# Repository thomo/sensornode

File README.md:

# SensorNode

A ESP8266 based solution with support for

- DS18B20 1-Wire temperature sensor
- BME280 humidity, pressure, temperature sensor (I2C) - Note: temperature is measured in-chip, so it is usually too inaccurate to measure the environment temperature
- Si7021 humidity, temperatur sensor (I2C)
- HTU21 humidity, temperatur sensor (I2C)
- LDR sensors to "measure" the brightness (analog)

The software will determine which sensors are connected. Because of the fixed I2C addresses on the sensors only one example of BME, Si7021, or HTU21 can be connected - but multiple different. Multiple 1-Wire sensors are supported. In total the number of sensors is set to 10 (`main.cpp`__MAX_SENSORS__) - but please note that each measurand counts, e.g. a BME280 counts 3x.

The software provides an configuration web page where the sensors can be enabled and an location can be specified.

The ESP will than read the sensors every 10 seconds (can be changed in config dialog). The values are published via MQTT (`main.cpp` __MQTT_SERVER__). The used MQTT topic can be configured by the configuration web page (see below).

## Compile time configuration

There are some values which are only configureable on compile time (in `main.cpp`).

- DEFAULT_NODE_NAME (= F42-NODE) - used as WiFi SSID
- MQTT_SERVER (= mqtt.thomo.de) - the MQTT server, you will have to use your own :wink:
- DEFAULT_ROOT_TOPIC (= "tmp") - the standard root topic
- MAX_SENSORS (= 10) - number of supported sensors

## Runtime configuration

The runtime configuration is done by using a configuration web page served by the node. Just enter *`http://<node-ip>`*.

The config dialog allows you to enable/disable (aka activate) the connected sensors, only active sensor values are MQTT published.
For each sensor a location can be defined and a correction value. The correction value is add/sub from the sensor value and is used to calibrate the sensor.

*Note:* The displayed sensor value and the value published at MQTT already include the correction value.

## API

The Sensor Node offers some URIs

- `http://<node-ip>/config` - the node name, root topic, altitude, and display flag, as JSON data
- `http://<node-ip>/sensors` - the sensor data, as JSON

## MQTT Topic and Payload

The node will acquire the sensor measurements every X seconds - wether or not the sensor is enabled. It will than publish the value to the MQTT server with:

- topic: `<root topic>/<location>` - where each dot '.' in the root topic and in location is replaced by a slash.
  
  E.g.: with root topic *homebase* and sensor location *ground.kitchen* the resulting topic is `homebase/ground/kitchen`.
- payload: `<measurand>,location=<sensor location>,node=<node name>,sensor=<sensor type> value=<sensor value>`

  E.g.: for the selected DS18B20 sensor above the payload is `temperature,location=upstairs.workroom,node=f42,sensor=DS18B20 value=25.25`

## Circuit and PCB designs

### Sensors

- I2C Sensors
  - SDA -> GPIO4 (D2)
  - SCL -> GPIO5 (D1)
- 1wire
  - DATA -> GPIO0 (D3)
- LDR
  - ADC (Pin2)

### Display

- ST7735 -> ESP8266
  - 1 - RST -> RST or +3V3
  - 2 - CS  -> GPIO15 (D8)  
  - 3 - D/C -> GPIO2 (D4)
  - 4 - DIN -> GPI13 (D7)
  - 5 - CLK -> GPI14 (D5)
  - 6 - VCC -> +3V3
  - 7 - BL  -> +3V3
  - 8 - GND -> GND

__Note:__ _GPIO12 (D6) is not connected but is part of the SPI interface._

### SensorNodeUsb

It is a board to be used with the sensor node code. The board is designed to be simply plugged in an USB port.

If you want to order some pcb boards you can use this link to [Aisler](https://aisler.net/p/KDLFHCIK).

### SensorNodeCat

Another board I designed to be placed in a CAT box, but it can also be used in a more general way.

If you want to order some pcb boards you can use this link to [Aisler](
https://aisler.net/p/CNWEPDIW).

## Fonts/Icons

- Font: [Landasans](https://www.fontspace.com/search?q=landasans)
- Icons:
  - https://iconarchive.com/search?q=weather&page=6
  - https://www.elegantthemes.com/blog/freebie-of-the-week/beautiful-flat-icons-for-free
  - http://paomedia.github.io/small-n-flat/

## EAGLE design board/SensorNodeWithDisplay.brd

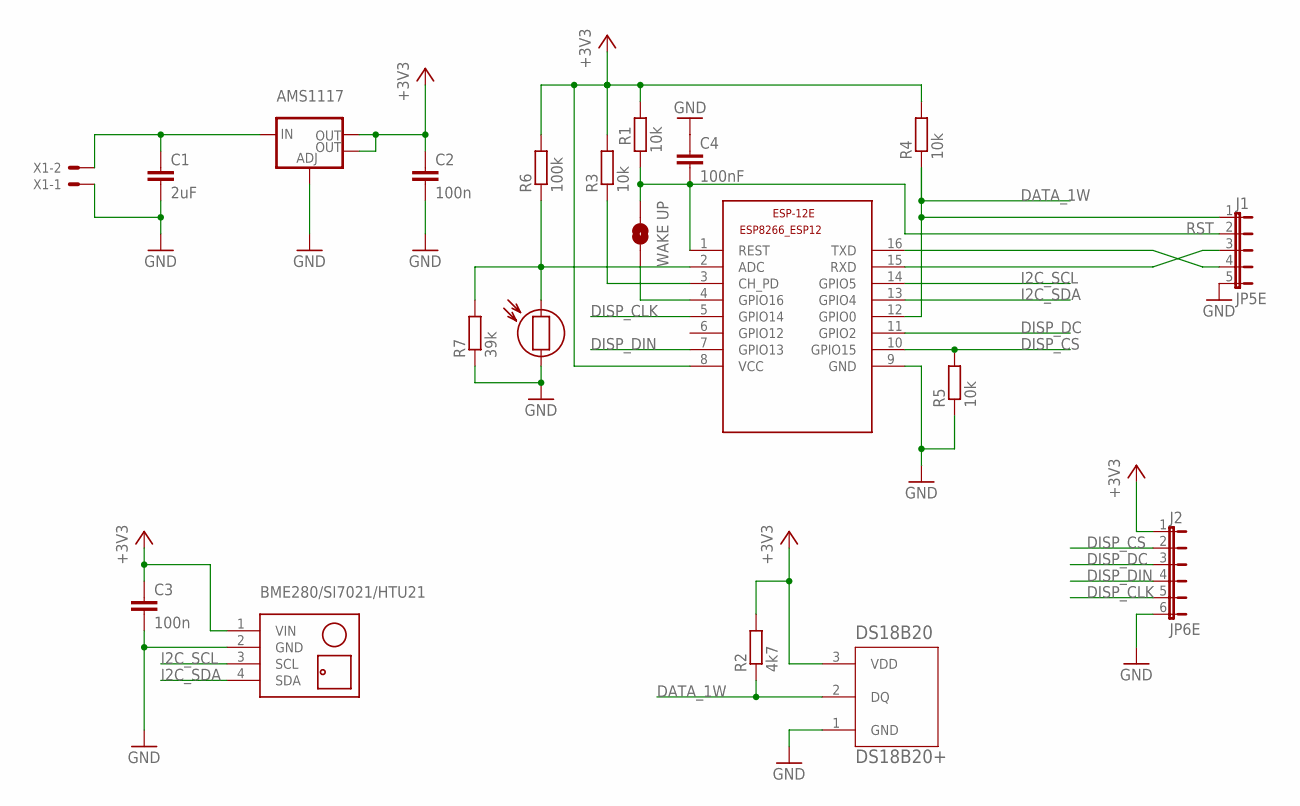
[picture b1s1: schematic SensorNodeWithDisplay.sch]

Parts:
AMS1117: V_REG_LM1117SOT223; SOT223
BME280/SI7021/HTU21: BME280
C1: 2uF; C1206
C2: 100n; C1206
C3: 100n; C1206K
C4: 100nF; C1206
DS18B20: DS18B20+; TO-92
ESP-12E: ESP8266-12; ESP8266-ESP12
J1: JP5E; JP5
J2: JP6E; JP6
LDR: LDR-GL55XX; GL55
R1, R3, R4, R5: 10k; M1206
R2: 4k7; M1206
R6: 100k; M1206
R7: 39k; M1206
WAKEUP: WAKE UP; SMT-JUMPER_2_NO_SILK
X1: JST-XH-02-PIN-LONG-PAD; JST-XH-02-PACKAGE-LONG-PAD

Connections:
+3V3: AMS1117.2 (OUT), AMS1117.4 (OUT), BME280/SI7021/HTU21.1 (VIN), C2.1, C3.1, DS18B20.3 (VDD), ESP-12E.8 (VCC), J2.1, R1.1, R2.2, R3.2, R4.2, R6.2
DATA_1W: DS18B20.2 (DQ), ESP-12E.12 (GPIO0), J1.1, R2.1, R4.1
DISP_CLK: ESP-12E.5 (GPIO14), J2.5
DISP_CS: ESP-12E.10 (GPIO15), J2.2, R5.2
DISP_DC: ESP-12E.11 (GPIO2), J2.3
DISP_DIN: ESP-12E.7 (GPIO13), J2.4
GND: AMS1117.1 (ADJ), BME280/SI7021/HTU21.2 (GND), C1.2, C2.2, C3.2, C4.1, DS18B20.1 (GND), ESP-12E.9 (GND), J1.5, J2.6, LDR.2, R5.1, R7.1, X1.1
I2C_SCL: BME280/SI7021/HTU21.3 (SCL), ESP-12E.14 (GPIO5)
I2C_SDA: BME280/SI7021/HTU21.4 (SDA), ESP-12E.13 (GPIO4)
unnamed: ESP-12E.15 (RXD), J1.3
unnamed: ESP-12E.4 (GPIO16), WAKEUP.1
unnamed: ESP-12E.3 (CH_PD), R3.1
unnamed: ESP-12E.16 (TXD), J1.4
unnamed: ESP-12E.2 (ADC), LDR.1, R6.1, R7.2
unnamed: AMS1117.3 (IN), C1.1, X1.2
RST: C4.2, ESP-12E.1 (REST), J1.2, R1.2, WAKEUP.2

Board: 2 copper layers, 24 parts (0 on the bottom side), 16 nets, no tracks yet.

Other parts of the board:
U$1, U$2, U$3, U$5: 3,0

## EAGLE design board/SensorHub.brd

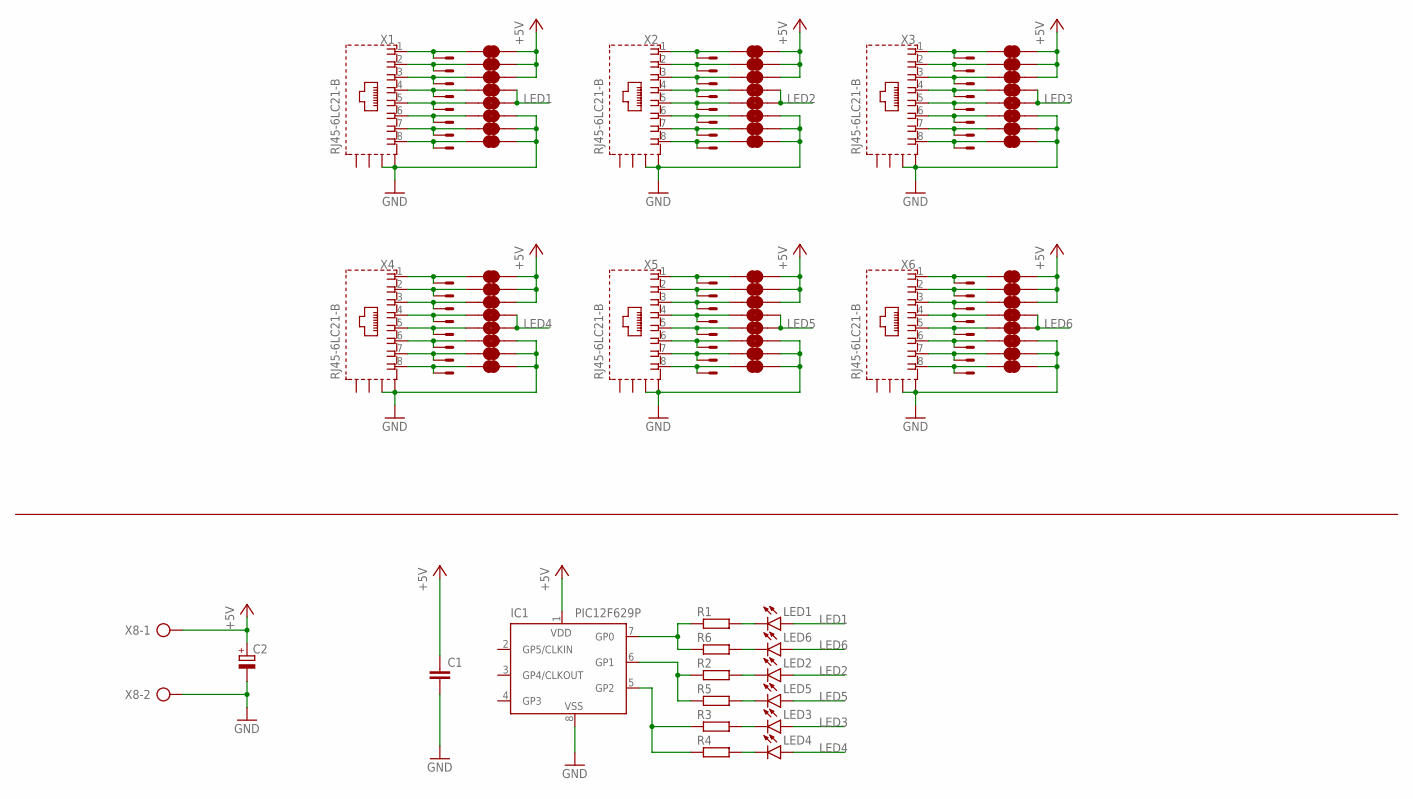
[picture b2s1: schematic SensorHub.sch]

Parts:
C1: C-EU050-024X044; C050-024X044
C2: CPOL-EUE3.5-8; E3,5-8
IC1: PIC12F629P; DIL8
JP1, JP2, JP3, JP4, JP5, JP6, JP7, JP8, JP9, JP10, JP11, JP12, JP13, JP14, JP15, JP16, JP17, JP18, JP19, JP20, JP21, JP22, JP23, JP24, JP25, JP26, JP27, JP28, JP29, JP30, JP31, JP32, JP33, JP34, JP35, JP36, JP37, JP38, JP39, JP40, JP41, JP42, JP43, JP44, JP45, JP46, JP47, JP48: JUMPER-SMT_2_NC_TRACE_SILK; SMT-JUMPER_2_NC_TRACE_SILK
LED1, LED2, LED3, LED4, LED5, LED6: TLLR4400; LED3MM
R1, R2, R3, R4, R5, R6: R-EU_0207/10; 0207/10
X1, X2, X3, X4, X5, X6: RJ45-6LC21-B; RJ45-SHIELD1
X1.1, X1.2, X1.3, X1.4, X1.5, X1.6: 22-23-2081
X8: AK500/2

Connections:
+5V: C1.1, C2.+, IC1.1 (VDD), JP1.2, JP2.2, JP3.2, JP9.2, JP10.2, JP11.2, JP17.2, JP18.2, JP19.2, JP25.2, JP26.2, JP27.2, JP33.2, JP34.2, JP35.2, JP41.2, JP42.2, JP43.2, X8.1
GND: C1.2, C2.-, IC1.8 (VSS), JP6.2, JP7.2, JP8.2, JP14.2, JP15.2, JP16.2, JP22.2, JP23.2, JP24.2, JP30.2, JP31.2, JP32.2, JP38.2, JP39.2, JP40.2, JP46.2, JP47.2, JP48.2, X1.S1 (S), X1.S2 (S), X2.S1 (S), X2.S2 (S), X3.S1 (S), X3.S2 (S), X4.S1 (S), X4.S2 (S), X5.S1 (S), X5.S2 (S), X6.S1 (S), X6.S2 (S), X8.2
LED1: JP4.2, JP5.2, LED1.A
LED2: JP12.2, JP13.2, LED2.A
LED3: JP20.2, JP21.2, LED3.A
LED4: JP28.2, JP29.2, LED4.A
LED5: JP36.2, JP37.2, LED5.A
LED6: JP44.2, JP45.2, LED6.A
unnamed: JP1.1, X1.1, X1.1.1
unnamed: JP2.1, X1.2, X1.1.2
unnamed: JP3.1, X1.3, X1.1.3
unnamed: JP4.1, X1.4, X1.1.4
unnamed: JP5.1, X1.5, X1.1.5
unnamed: JP6.1, X1.6, X1.1.6
unnamed: JP7.1, X1.7, X1.1.7
unnamed: JP8.1, X1.8, X1.1.8
unnamed: JP9.1, X1.2.1, X2.1
unnamed: IC1.6 (GP1), R2.1, R5.1
unnamed: LED1.K (C), R1.2
unnamed: LED2.K (C), R2.2
unnamed: LED3.K (C), R3.2
unnamed: LED6.K (C), R6.2
unnamed: LED5.K (C), R5.2
unnamed: LED4.K (C), R4.2
unnamed: JP10.1, X1.2.2, X2.2
unnamed: JP11.1, X1.2.3, X2.3
unnamed: JP12.1, X1.2.4, X2.4
unnamed: IC1.7 (GP0), R1.1, R6.1
unnamed: JP13.1, X1.2.5, X2.5
unnamed: IC1.5 (GP2), R3.1, R4.1
unnamed: JP14.1, X1.2.6, X2.6
unnamed: JP15.1, X1.2.7, X2.7
unnamed: JP16.1, X1.2.8, X2.8
unnamed: JP17.1, X1.3.1, X3.1
unnamed: JP18.1, X1.3.2, X3.2
unnamed: JP19.1, X1.3.3, X3.3
unnamed: JP20.1, X1.3.4, X3.4
unnamed: JP21.1, X1.3.5, X3.5
unnamed: JP22.1, X1.3.6, X3.6
unnamed: JP23.1, X1.3.7, X3.7
unnamed: JP24.1, X1.3.8, X3.8
unnamed: JP25.1, X1.4.1, X4.1
unnamed: JP26.1, X1.4.2, X4.2
unnamed: JP27.1, X1.4.3, X4.3
unnamed: JP28.1, X1.4.4, X4.4
unnamed: JP29.1, X1.4.5, X4.5
unnamed: JP30.1, X1.4.6, X4.6
unnamed: JP31.1, X1.4.7, X4.7
unnamed: JP32.1, X1.4.8, X4.8
unnamed: JP33.1, X1.5.1, X5.1
unnamed: JP34.1, X1.5.2, X5.2
unnamed: JP35.1, X1.5.3, X5.3
unnamed: JP36.1, X1.5.4, X5.4
unnamed: JP37.1, X1.5.5, X5.5
unnamed: JP38.1, X1.5.6, X5.6
unnamed: JP39.1, X1.5.7, X5.7
unnamed: JP40.1, X1.5.8, X5.8
unnamed: JP41.1, X1.6.1, X6.1
unnamed: JP42.1, X1.6.2, X6.2
unnamed: JP43.1, X1.6.3, X6.3
unnamed: JP44.1, X1.6.4, X6.4
unnamed: JP45.1, X1.6.5, X6.5
unnamed: JP46.1, X1.6.6, X6.6
unnamed: JP47.1, X1.6.7, X6.7
unnamed: JP48.1, X1.6.8, X6.8

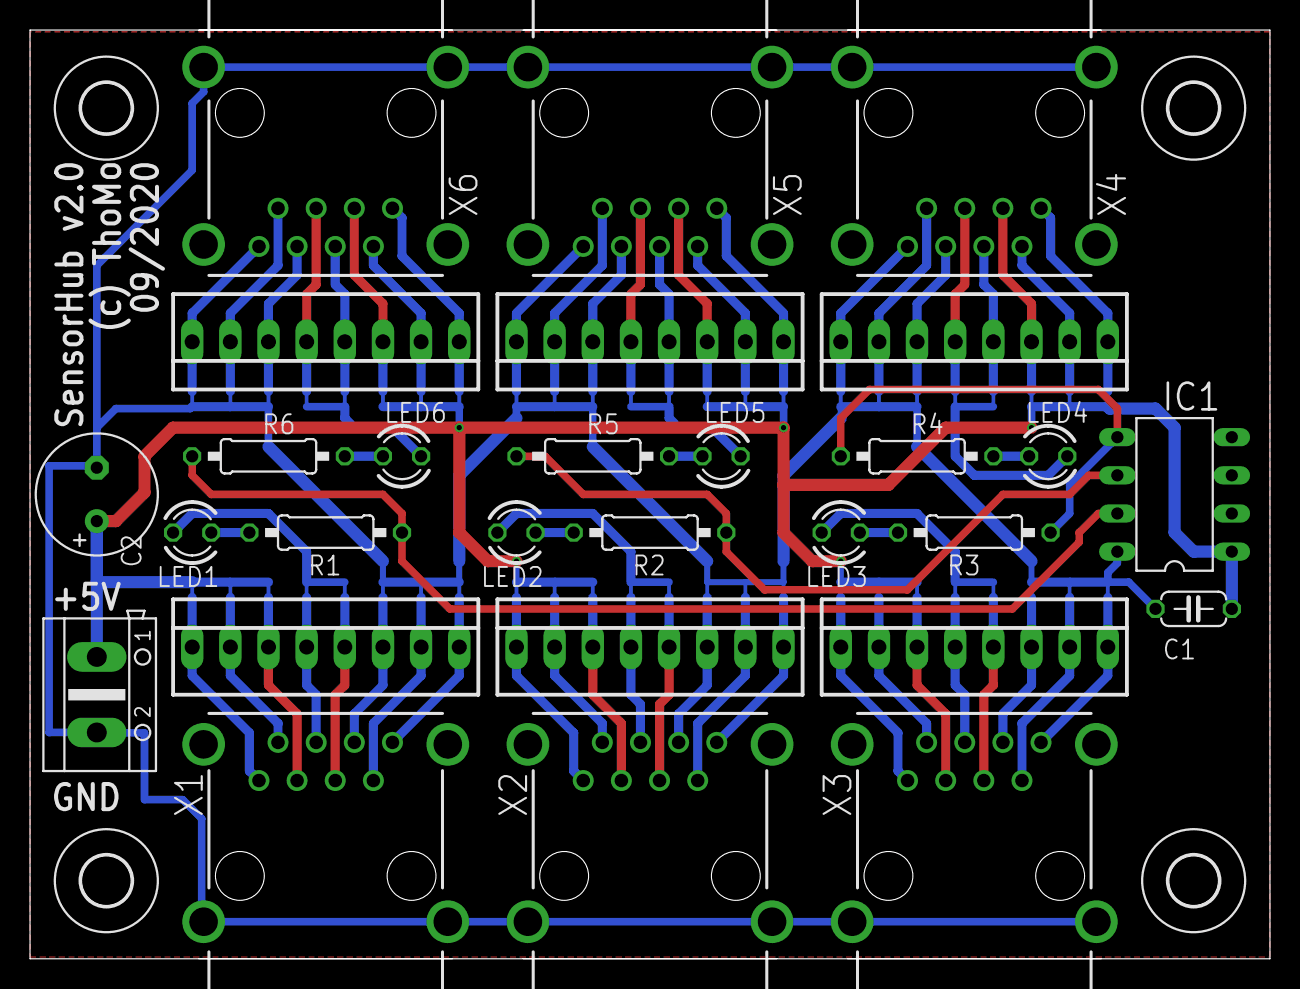
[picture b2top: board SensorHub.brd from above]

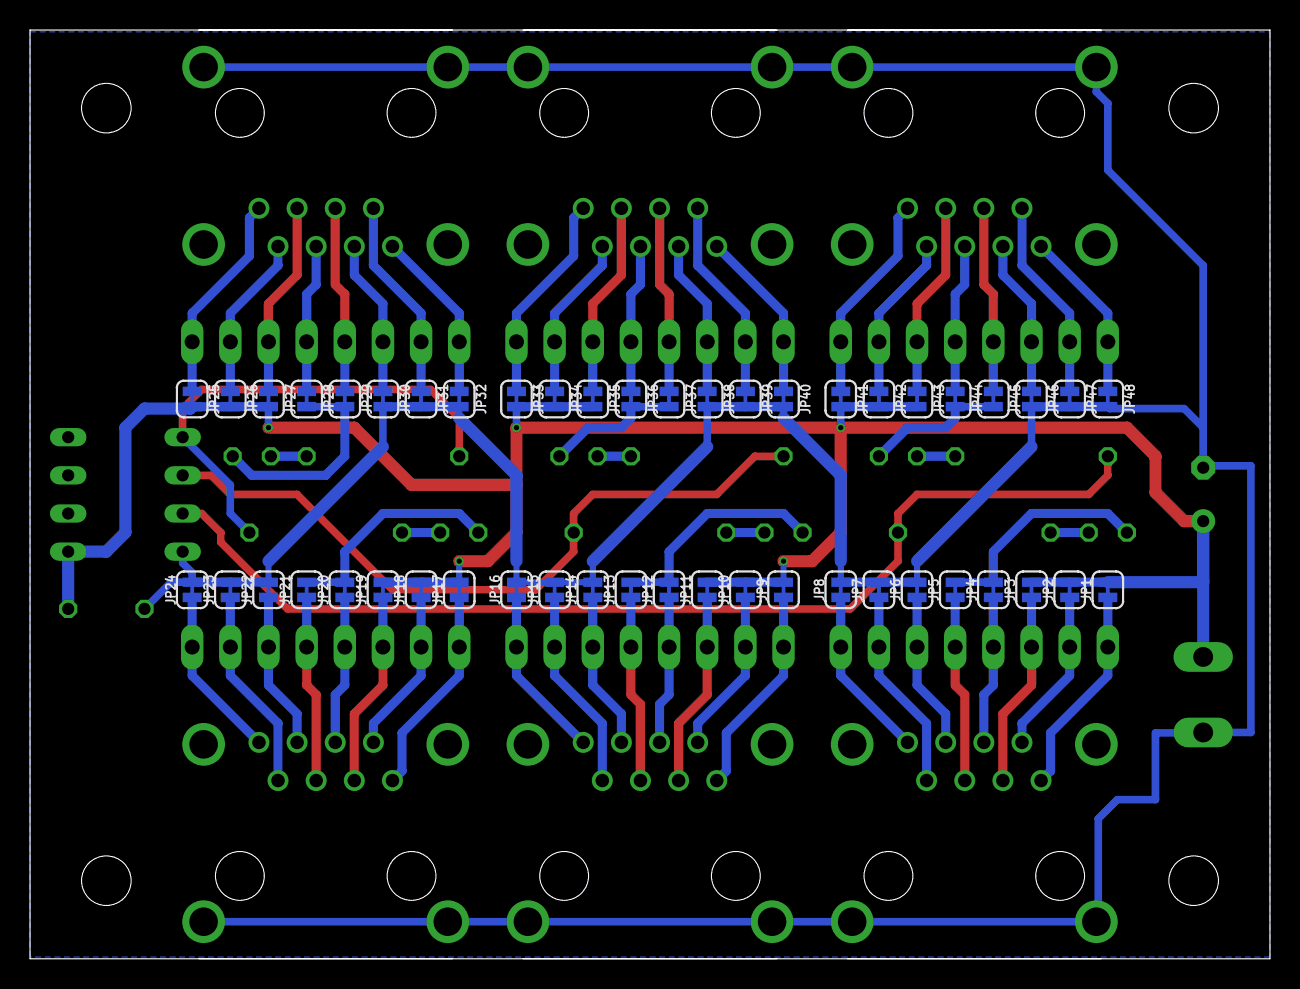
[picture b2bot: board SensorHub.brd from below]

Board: 2 copper layers, 82.5 x 61.8 mm, 80 parts (48 on the bottom side), 65 nets.

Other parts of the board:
U$1, U$2, U$3, U$4: 3,3

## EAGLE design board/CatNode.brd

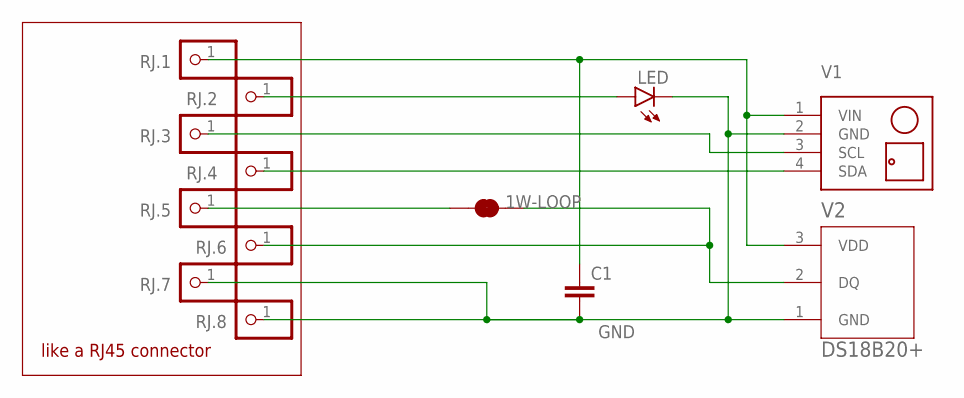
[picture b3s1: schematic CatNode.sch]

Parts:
1W-LOOP: JUMPER-SMT_2_NC_TRACE_SILK; SMT-JUMPER_2_NC_TRACE_SILK
C1: C-EUC0805; C0805
LED: LEDSML0805; SML0805
RJ.1, RJ.2, RJ.3, RJ.4, RJ.5, RJ.6, RJ.7, RJ.8: PINHD-1X1; 1X01
V1: TEMP-HUM-PRES-BME280
V2: DS18B20+; TO-92

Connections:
GND: C1.2, LED.C, RJ.7.1, RJ.8.1, V1.2 (GND), V2.1 (GND)
unnamed: C1.1, RJ.1.1, V1.1 (VIN), V2.3 (VDD)
unnamed: RJ.4.1, V1.4 (SDA)
unnamed: LED.A, RJ.2.1
unnamed: RJ.3.1, V1.3 (SCL)
unnamed: 1W-LOOP.1, RJ.5.1
unnamed: 1W-LOOP.2, RJ.6.1, V2.2 (DQ)

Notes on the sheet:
like a RJ45 connector

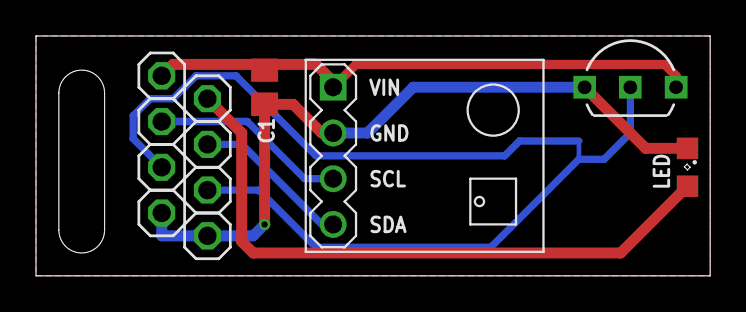
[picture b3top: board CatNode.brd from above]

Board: 2 copper layers, 37.5 x 13.3 mm, 13 parts (1 on the bottom side), 7 nets.

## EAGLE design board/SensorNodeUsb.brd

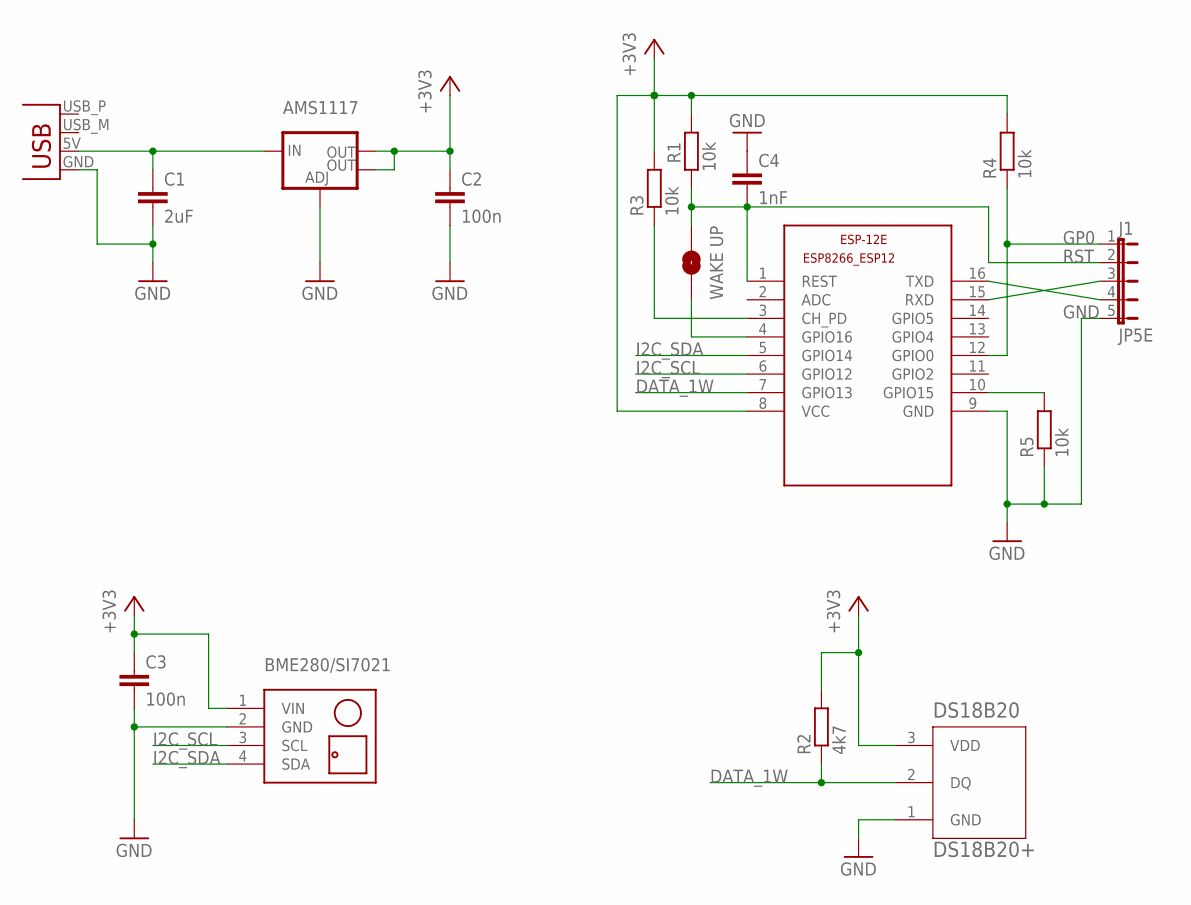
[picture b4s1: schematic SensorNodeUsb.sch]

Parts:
AMS1117: V_REG_LM1117SOT223; SOT223
BME280/SI7021: TEMP-HUM-PRES-BME280
C1: 2uF; C1206
C2: 100n; C1206
C3: 100n; C1206K
C4: 1nF; C1206
DS18B20: DS18B20+; TO-92
ESP-12E: ESP8266-12; ESP8266-ESP12
J1: JP5E; JP5
R1, R3, R4, R5: 10k; M1206
R2: 4k7; M1206
WAKEUP: WAKE UP; SMT-JUMPER_2_NO_SILK
X2: USBPCB; USB-A-PCB

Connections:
+3V3: AMS1117.2 (OUT), AMS1117.4 (OUT), BME280/SI7021.1 (VIN), C2.1, C3.1, DS18B20.3 (VDD), ESP-12E.8 (VCC), R1.1, R2.2, R3.2, R4.2
DATA_1W: DS18B20.2 (DQ), ESP-12E.7 (GPIO13), R2.1
GND: AMS1117.1 (ADJ), BME280/SI7021.2 (GND), C1.2, C2.2, C3.2, C4.1, DS18B20.1 (GND), ESP-12E.9 (GND), J1.5, R5.1, X2.GND
GP0: ESP-12E.12 (GPIO0), J1.1, R4.1
I2C_SCL: BME280/SI7021.3 (SCL), ESP-12E.6 (GPIO12)
I2C_SDA: BME280/SI7021.4 (SDA), ESP-12E.5 (GPIO14)
unnamed: ESP-12E.15 (RXD), J1.3
unnamed: ESP-12E.4 (GPIO16), WAKEUP.1
unnamed: ESP-12E.3 (CH_PD), R3.1
unnamed: ESP-12E.16 (TXD), J1.4
unnamed: AMS1117.3 (IN), C1.1, X2.5V (VBUS)
unnamed: ESP-12E.10 (GPIO15), R5.2
RST: C4.2, ESP-12E.1 (REST), J1.2, R1.2, WAKEUP.2

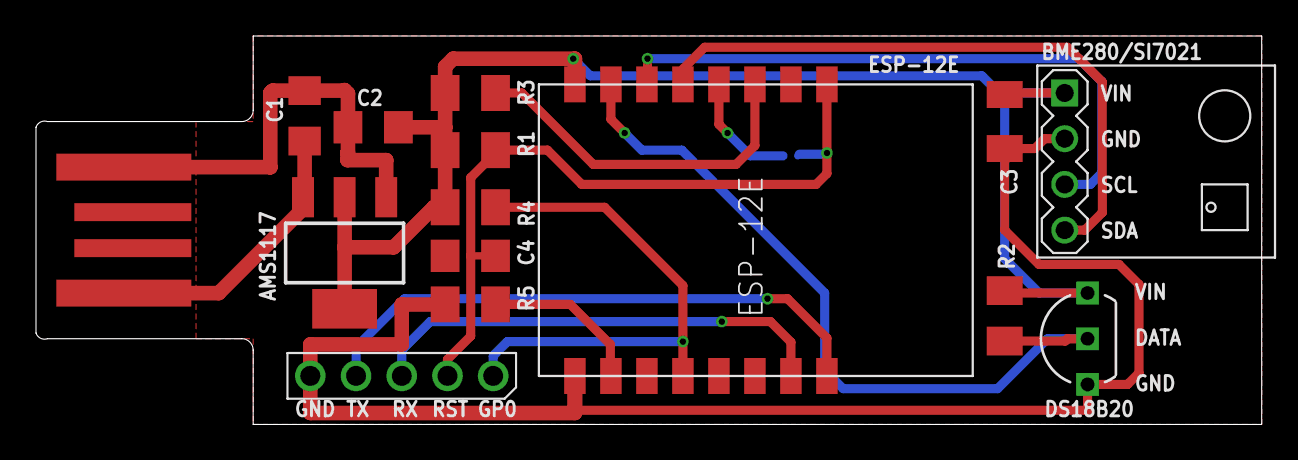
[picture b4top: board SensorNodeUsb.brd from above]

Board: 2 copper layers, 68.1 x 21.6 mm, 16 parts (1 on the bottom side), 13 nets.

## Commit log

2019-03-30 init
2019-03-30 save config
2019-03-30 cyclic acquisition of sensor data
2019-03-31 replace location by node, introduce measurand
2019-03-31 support measurand
2019-04-01 prepare sensor output
2019-04-01 use sensor location instead of sensor name
2019-04-01 append topic to SensorData
2019-04-06 add mqtt stuff
2019-04-07 replase WiFiServer by ESP8266WebServer
2019-04-07 add dynamic root topic
2019-04-07 store and update roottopic in sensortopic
2019-04-07 publish sensor data by mqtt
2019-04-09 add BME support
2019-04-13 add enabled flag to sensors
2019-04-13 redesign form and load/save enable flag
2019-04-14 eval en flag in post request & when sending mqtt msg
2019-04-27 add Si7021 support
2019-04-27 improve debug messages
2019-04-27 fix load config issue
2019-04-27 improve serial messages
2019-04-28 add pcb stuff and begin with docu
2019-04-28 add LICENSE
2019-04-28 add summary and notes about compile time configuration
2019-04-29 add description of MQTT topic and payload
2019-05-01 ignore Eagle backup files
2019-05-01 modify adjust a part name and a part value
2019-05-01 remove 2 vias near R2
2019-05-01 add note about used MQTT server
2019-05-01 use relative path to config image
2019-05-01 rename circuit file
2019-05-01 crop images
2019-05-01 add SensorNodeUsb circuit and board description and image links
2019-06-18 add internal temp sensor to available sensors
2019-07-13 5-pin programming interface
2019-07-14 change programming interface
2019-07-14 change a message and increase max no. of sensors
2019-07-14 ignore PLATFORMIO files
2019-07-14 add link to AISLER
2019-07-23 set Ticker library version
2019-07-23 use const to provide string parameter to functions
2019-07-23 init struct and explicit cast
2019-07-23 initial config file (intentionally empty)
2019-07-23 init topic field in sensors array
2019-07-23 change max number of sensors
2019-07-24 add 3d model of usb spacer plate
2019-07-27 rename deviceCount variable to oneWireDeviceCount
2019-07-28 place values on board
2019-07-28 add correction values and configurable altitude
2019-07-28 update docu
2020-01-23 SensorHub PCB files
2020-01-23 CatNode pcb files
2020-01-23 init version of PIC files
2020-09-20 sensor hub with power lines only
2020-10-15 use LittleFS
2020-10-16 add SensorNodeCat board
2020-10-16 add Sensor type HTU21
2020-10-16 add Display
2020-10-17 further boards
2020-10-17 update doc with HTU21 notes
2020-10-17 adapt new hub
2020-10-18 use OpenWeatherMap
2020-10-25 add further icons
2020-11-01 Add flag for different board layouts
2020-11-01 Introduce SENSORNODE_VERSION
2020-11-01 update jquery
2020-11-01 Make timeout configurable
2020-11-02 Add OTA
2020-11-02 Refactor saveConfig
2020-11-15 improve rest api
2021-01-02 add resistor parallel to LDR
2021-01-02 std config
2021-01-03 add LDR and text to PCB
2021-01-03 edit comment
2021-01-03 add logging and build info
2021-01-03 Fix config file log msg.
2021-01-09 improve WIFI log
2021-01-09 use PRGMEM
2021-01-30 Add notes about SensorNodeCat.
2021-01-30 Lint markdown
2021-01-30 Fix some details in description
2022-01-04 inline display
2022-02-19 use local hostalias for ntp and cdn
2023-03-22 update libs
2025-11-09 RSSI sensor

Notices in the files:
parts and their libraries:
SparkFun-Jumpers: Licensing: Creative Commons ShareAlike 4.0 International - https://creativecommons.org/licenses/by-sa/4.0
